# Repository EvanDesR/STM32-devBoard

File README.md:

# STM32-devBoard

At one point I was considering electrical or computer hardware engineering as a degree, but I decided to just keep it a hobby. This is most recent/best hardware project.

## Board design

## Connection plotter

## Did you know you can put corporate logos on PCBs, and JLCPCB wont complain?! 

## A closer look at the board layout. Designed with minimizing noise in mind.

## PCB render from development

## After finishing the .bom (bill of materials) file for JLCPCB, I submitted the design for approval, and manufactuering 

## About two weeks later...

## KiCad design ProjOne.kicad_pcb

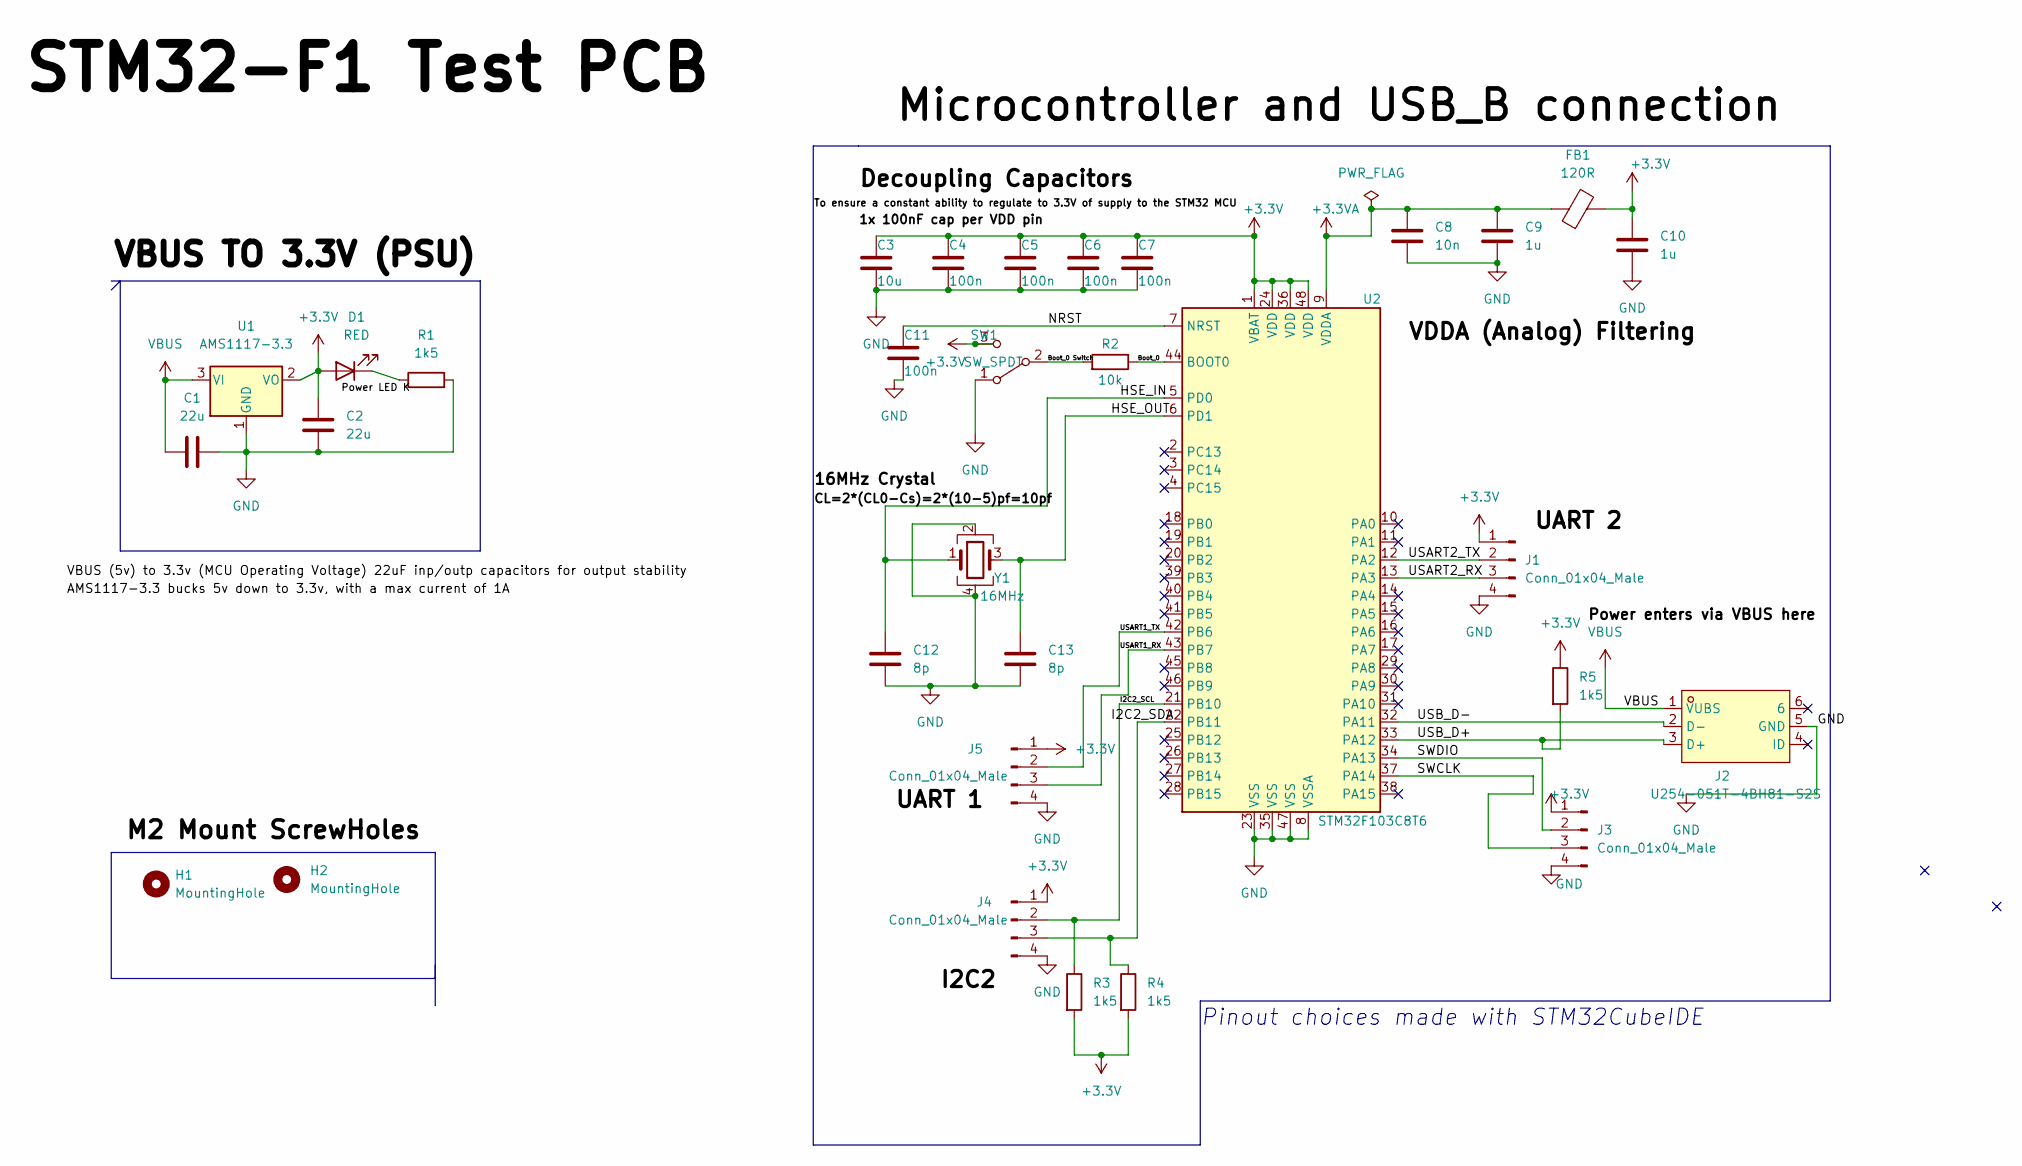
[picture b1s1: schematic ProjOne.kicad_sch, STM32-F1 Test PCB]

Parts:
C1, C2: 22u; C_0805_2012Metric; LCSC C45783
C3: 10u; C_0603_1608Metric_Pad1.08x0.95mm_HandSolder; LCSC C19702
C4, C5, C6, C7, C11: 100n; C_0402_1005Metric; LCSC C2981728
C8: 10n; C_0402_1005Metric; LCSC C15195
C9, C10: 1u; C_0402_1005Metric; LCSC C52923
C12, C13: 8p; C_0402_1005Metric; LCSC C342939
D1: RED; LED_0603_1608Metric; LCSC C2286
FB1: 120R; L_0805_2012Metric; LCSC C160964
H1, H2: MountingHole; MountingHole_2.2mm_M2
J1, J3, J4, J5: Conn_01x04_Male; PinHeader_1x04_P2.54mm_Vertical; LCSC C2691448
J2: U254-051T-4BH81-S2S; MICRO-USB-SMD_5P-P0.65-H-F_U254-051T-4BH81-S2S; LCSC Part C381144
R1, R3, R4, R5: 1k5; R_0402_1005Metric; LCSC C319978
R2: 10k; R_0402_1005Metric; LCSC C269701
SW1: SW_SPDT; SW_SPDT_PCM12; LCSC C5149818
U1: AMS1117-3.3; SOT-223-3_TabPin2; LCSC C6186
U2: STM32F103C8T6; LQFP-48_7x7mm_P0.5mm; LCSC C8734
Y1: 16MHz; Crystal_SMD_3225-4Pin_3.2x2.5mm; LCSC C129740

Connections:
+3.3VA: C8.1, C9.1, FB1.1, U2.9 (VDDA)
+3V3: C2.1, C3.1, C4.1, C5.1, C6.1, C7.1, C10.1, D1.2 (A), FB1.2, J1.1, J3.1, J4.1, J5.1, R3.2, R4.2, R5.1, SW1.3 (C), U1.2 (VO), U2.1 (VBAT), U2.24 (VDD), U2.36 (VDD), U2.48 (VDD)
/Boot_0: R2.1, U2.44 (BOOT0)
/Boot_0 Switch: R2.2, SW1.2 (B)
/HSE_IN: C12.1, U2.5 (PD0), Y1.1
/HSE_OUT: C13.1, U2.6 (PD1), Y1.3
/I2C2_SCL: J4.2, R3.1, U2.21 (PB10)
/NRST: C11.1, U2.7 (NRST)
/SWCLK: J3.3, U2.37 (PA14)
/SWDIO: J3.2, U2.34 (PA13)
/USART1_RX: J5.2, U2.42 (PB6)
/USART2_RX: J1.3, U2.13 (PA3)
/USART2_TX: J1.2, U2.12 (PA2)
/USB_D+: J2.3 (D+), R5.2, U2.33 (PA12)
/USB_D-: J2.2 (D-), U2.32 (PA11)
GND: C1.2, C2.2, C3.2, C4.2, C5.2, C6.2, C7.2, C8.2, C9.2, C10.2, C11.2, C12.2, C13.2, J1.4, J2.5 (GND), J3.4, J4.4, J5.4, R1.2, SW1.1 (A), U1.1 (GND), U2.8 (VSSA), U2.23 (VSS), U2.35 (VSS), U2.47 (VSS), Y1.2, Y1.4
unnamed: D1.1 (K), R1.1
unnamed: J4.3, R4.1, U2.22 (PB11)
unnamed: J5.3, U2.43 (PB7)
VBUS: C1.1, J2.1 (VUBS), U1.3 (VI)

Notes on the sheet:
Pinout choices made with STM32CubeIDE

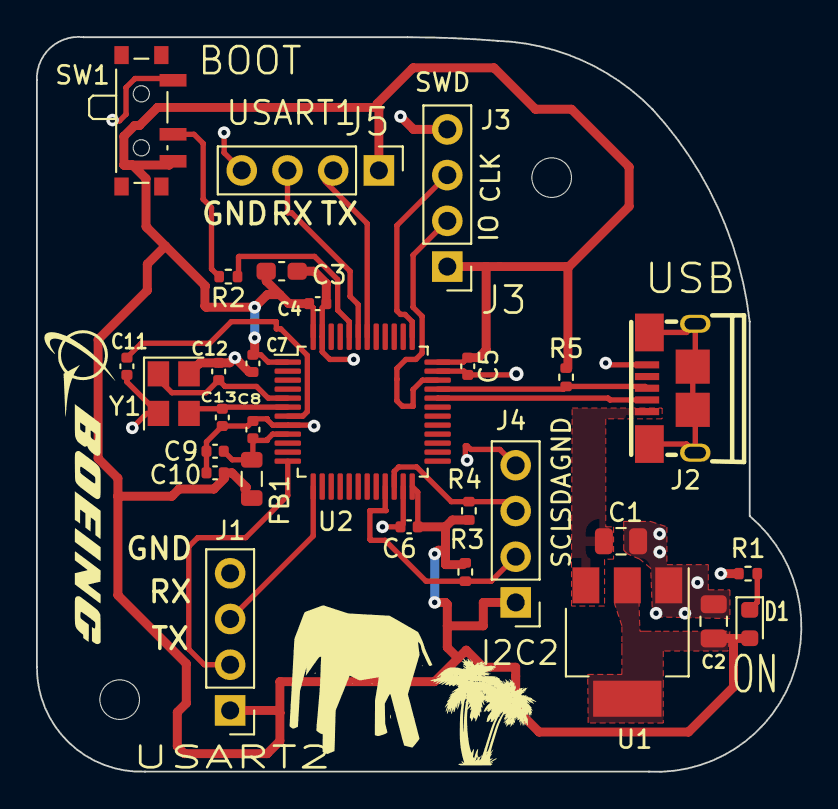
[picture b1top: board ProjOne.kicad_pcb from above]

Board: 2 copper layers, 42.5 x 40.8 mm, 31 parts (0 on the bottom side), 20 nets.

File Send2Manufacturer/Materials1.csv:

"Source:","/home/wockyslush/kicads/ProjOne/ProjOne.kicad_sch"
"Date:","Tue 26 Mar 2024 10:59:46 PM"
"Tool:","Eeschema 6.0.2+dfsg-1"
"Generator:","/usr/share/kicad/plugins/bom_csv_grouped_by_value_with_fp.py"
"Component Count:","31"
"Ref","Qnty","Value","Cmp name","Footprint","Description","Vendor"
"C1, C2, ","2","22u","C","Capacitor_SMD:C_0805_2012Metric","Unpolarized capacitor",""
"C3, ","1","10u","C","Capacitor_SMD:C_0603_1608Metric_Pad1.08x0.95mm_HandSolder","Unpolarized capacitor",""
"C4, C5, C6, C7, C11, ","5","100n","C","Capacitor_SMD:C_0402_1005Metric","Unpolarized capacitor",""
"C8, ","1","10n","C","Capacitor_SMD:C_0402_1005Metric","Unpolarized capacitor",""
"C9, C10, ","2","1u","C","Capacitor_SMD:C_0402_1005Metric","Unpolarized capacitor",""
"C12, C13, ","2","10p","C","Capacitor_SMD:C_0402_1005Metric","Unpolarized capacitor",""
"D1, ","1","RED","LED","LED_SMD:LED_0603_1608Metric","Light emitting diode",""
"FB1, ","1","120R","FerriteBead","Inductor_SMD:L_0201_0603Metric","Ferrite bead",""
"J1, J3, J5, ","3","Conn_01x04_Male","Conn_01x04_Male","Connector_PinHeader_2.54mm:PinHeader_1x04_P2.54mm_Vertical","Generic connector, single row, 01x04, script generated (kicad-library-utils/schlib/autogen/connector/)",""
"J2, ","1","USB_B_Micro","USB_B_Micro","Connector_USB:USB_Micro-B_Wuerth_629105150521","USB Micro Type B connector",""
"J4, ","1","Conn_01x04_Male ","Conn_01x04_Male","Connector_PinHeader_2.54mm:PinHeader_1x04_P2.54mm_Vertical","Generic connector, single row, 01x04, script generated (kicad-library-utils/schlib/autogen/connector/)",""
"R1, R3, R4, R5, ","4","1k5","R","Resistor_SMD:R_0402_1005Metric","Resistor",""
"R2, ","1","10k ","R","Resistor_SMD:R_0402_1005Metric","Resistor",""
"SW1, ","1","SW_SPDT","SW_SPDT","Button_Switch_THT:SW_E-Switch_EG1224_SPDT_Angled","Switch, single pole double throw",""
"U1, ","1","AMS1117-3.3","AMS1117-3.3","Package_TO_SOT_SMD:SOT-223-3_TabPin2","1A Low Dropout regulator, positive, 3.3V fixed output, SOT-223",""
"U2, ","1","STM32F103C8T6","STM32F103C8Tx","Package_QFP:LQFP-48_7x7mm_P0.5mm","ARM Cortex-M3 MCU, 64KB flash, 20KB RAM, 72MHz, 2-3.6V, 37 GPIO, LQFP-48",""
"Y1, ","1","16MHz","Crystal_GND24","Crystal:Crystal_SMD_3225-4Pin_3.2x2.5mm","Four pin crystal, GND on pins 2 and 4",""

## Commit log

2025-02-11 Files Added
    STM32 based development breakout board. Primarily being uploaded as proof of work.
2025-02-11 Update README.md
    images for readme
